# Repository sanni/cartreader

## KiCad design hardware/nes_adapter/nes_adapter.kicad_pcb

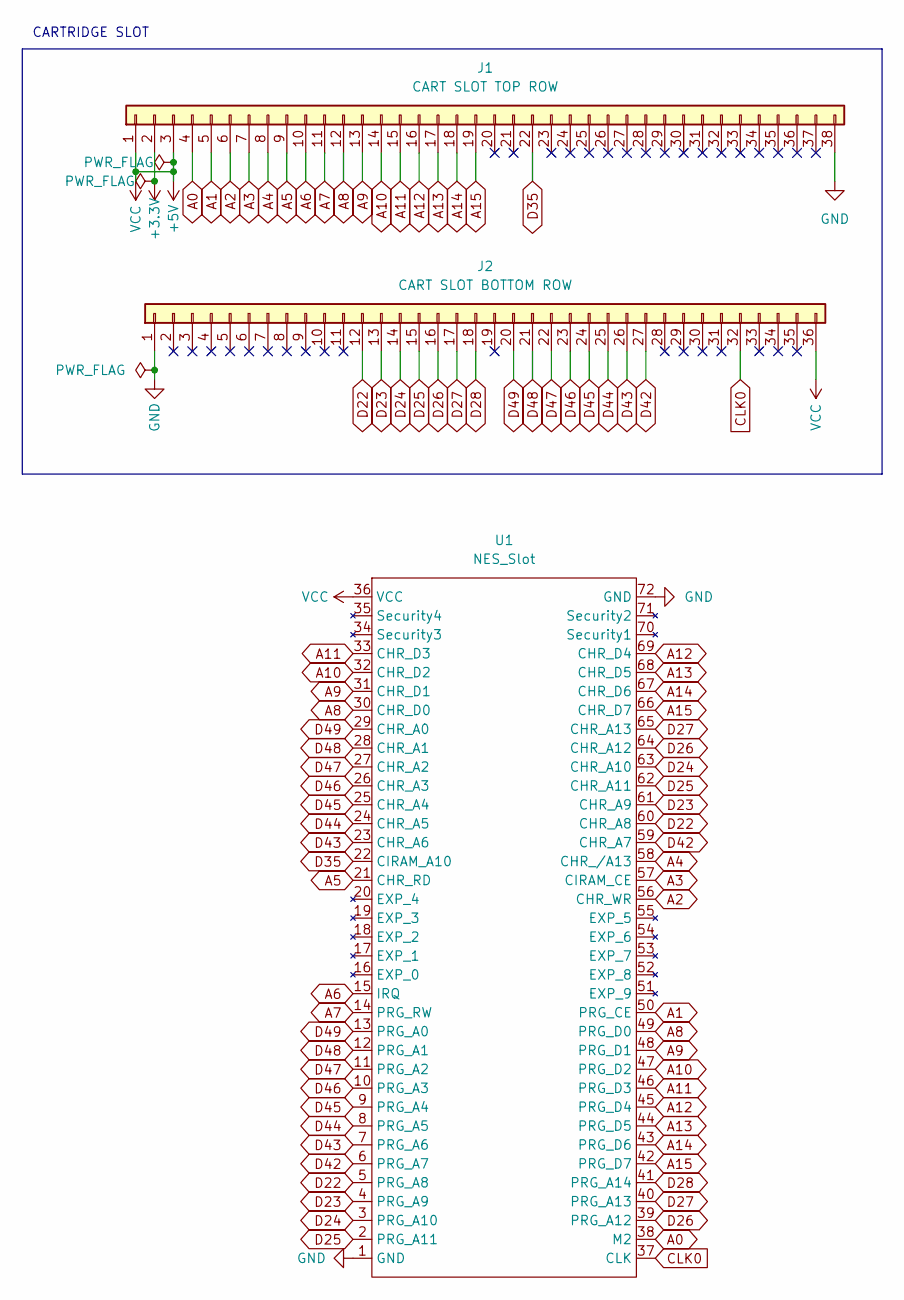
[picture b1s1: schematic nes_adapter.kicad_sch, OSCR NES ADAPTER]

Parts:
J1: CART SLOT TOP ROW; PinSocket_1x38_P2.54mm_Vertical
J2: CART SLOT BOTTOM ROW; PinSocket_1x36_P2.54mm_Vertical
U1: NES_Slot

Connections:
+3V3: J1.2
+5V: J1.1, J1.3, J2.36, U1.36 (VCC)
A0: J1.4, U1.38 (M2)
A1: J1.5, U1.50 (PRG_CE)
A2: J1.6, U1.56 (CHR_WR)
A3: J1.7, U1.57 (CIRAM_CE)
A4: J1.8, U1.58 (CHR_/A13)
A5: J1.9, U1.21 (CHR_RD)
A6: J1.10, U1.15 (IRQ)
A7: J1.11, U1.14 (PRG_RW)
A8: J1.12, U1.30 (CHR_D0), U1.49 (PRG_D0)
A9: J1.13, U1.31 (CHR_D1), U1.48 (PRG_D1)
A10: J1.14, U1.32 (CHR_D2), U1.47 (PRG_D2)
A11: J1.15, U1.33 (CHR_D3), U1.46 (PRG_D3)
A12: J1.16, U1.45 (PRG_D4), U1.69 (CHR_D4)
A13: J1.17, U1.44 (PRG_D5), U1.68 (CHR_D5)
A14: J1.18, U1.43 (PRG_D6), U1.67 (CHR_D6)
A15: J1.19, U1.42 (PRG_D7), U1.66 (CHR_D7)
CLK0: J2.32, U1.37 (CLK)
D22: J2.12, U1.5 (PRG_A8), U1.60 (CHR_A8)
D23: J2.13, U1.4 (PRG_A9), U1.61 (CHR_A9)
D24: J2.14, U1.3 (PRG_A10), U1.63 (CHR_A10)
D25: J2.15, U1.2 (PRG_A11), U1.62 (CHR_A11)
D26: J2.16, U1.39 (PRG_A12), U1.64 (CHR_A12)
D27: J2.17, U1.40 (PRG_A13), U1.65 (CHR_A13)
D28: J2.18, U1.41 (PRG_A14)
D35: J1.22, U1.22 (CIRAM_A10)
D42: J2.27, U1.6 (PRG_A7), U1.59 (CHR_A7)
D43: J2.26, U1.7 (PRG_A6), U1.23 (CHR_A6)
D44: J2.25, U1.8 (PRG_A5), U1.24 (CHR_A5)
D45: J2.24, U1.9 (PRG_A4), U1.25 (CHR_A4)
D46: J2.23, U1.10 (PRG_A3), U1.26 (CHR_A3)
D47: J2.22, U1.11 (PRG_A2), U1.27 (CHR_A2)
D48: J2.21, U1.12 (PRG_A1), U1.28 (CHR_A1)
D49: J2.20, U1.13 (PRG_A0), U1.29 (CHR_A0)
GND: J1.38, J2.1, U1.1 (GND), U1.72 (GND)

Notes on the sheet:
CARTRIDGE SLOT

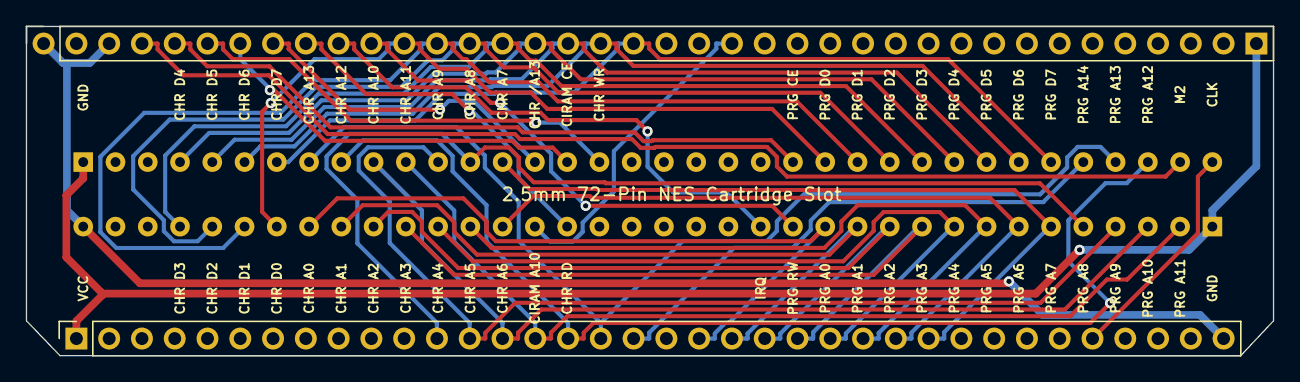
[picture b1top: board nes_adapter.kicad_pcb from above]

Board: 2 copper layers, 96.6 x 25.5 mm, 3 parts (0 on the bottom side), 35 nets.

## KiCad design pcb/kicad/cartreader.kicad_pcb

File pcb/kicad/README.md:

You can view the schematic and the PCB files using a free and open source programm called [KiCad](https://www.kicad.org/).

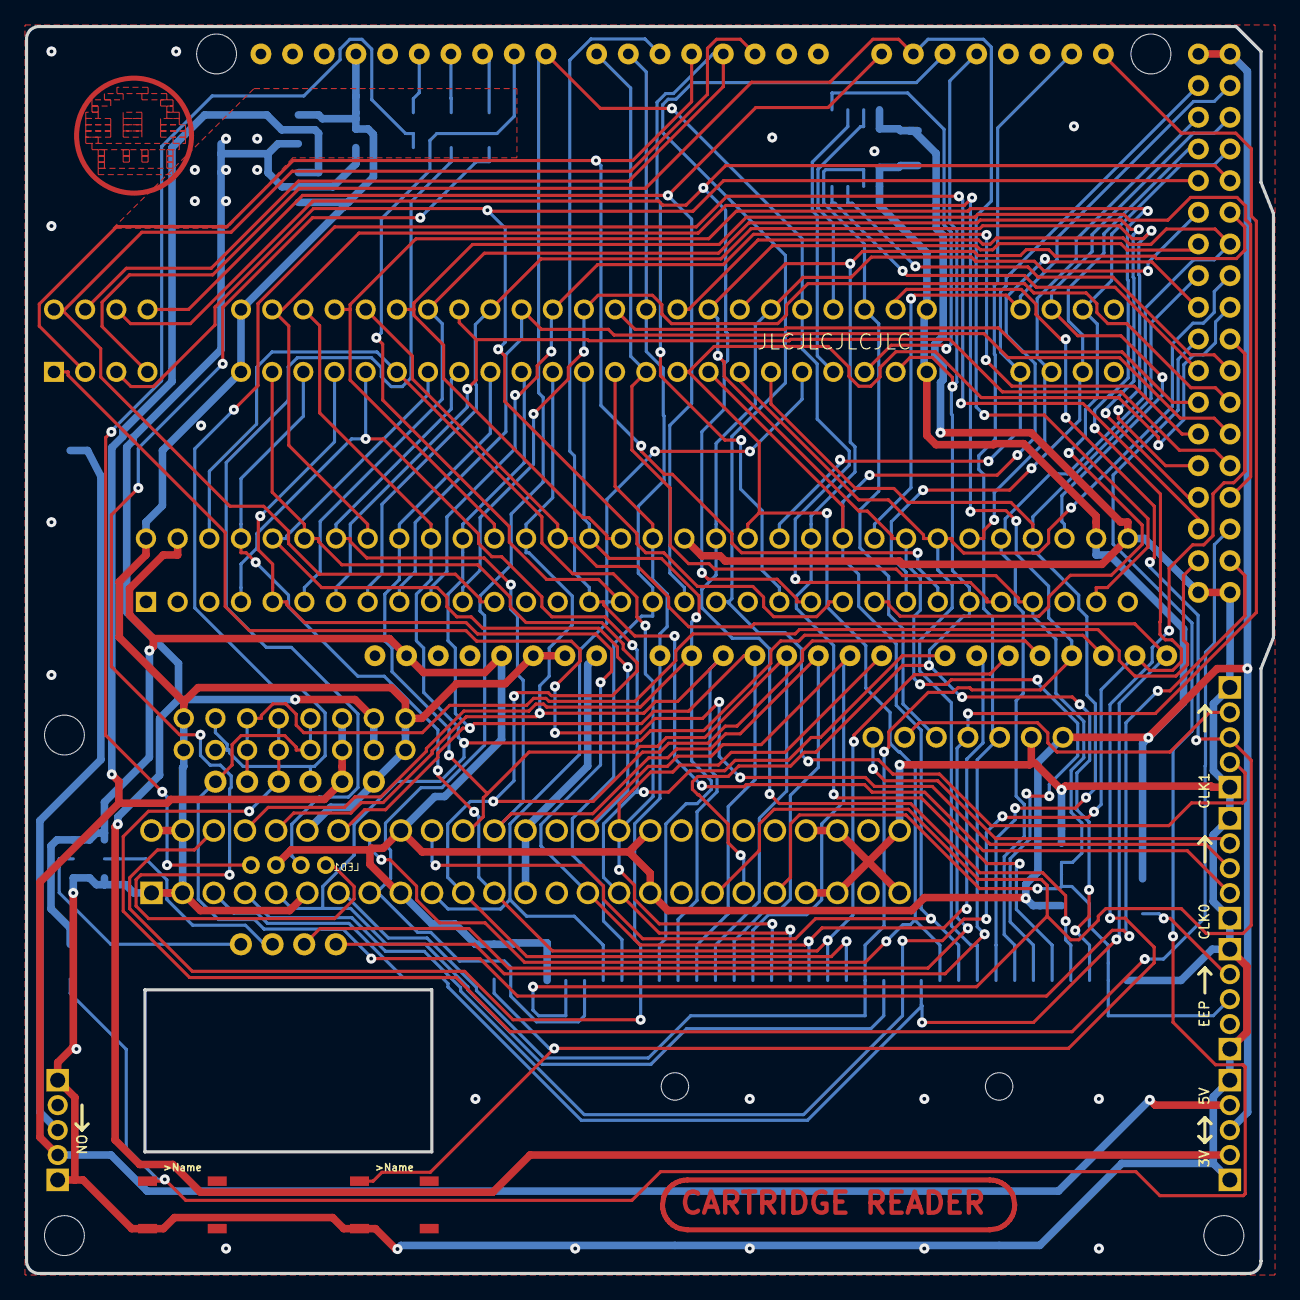
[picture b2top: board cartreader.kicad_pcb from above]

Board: 2 copper layers, 100.0 x 100.0 mm, 46 parts (0 on the bottom side), 85 nets.

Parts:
1K1, 10K1, 220R1, 1000R1: R-US_M1206; M1206
100NF1: C-USC1206; C1206
+22UF1: C-USC1206; C1206
@HOLE0, @HOLE1, @HOLE2, @HOLE3, @HOLE4: (no value)
ADCH1: 8x1F-H8.5; 1X08
ADCL1: 8x1F-H8.5; 1X08
AMS1117-3V3: SMD-AMS1117SOT223; SOT223
CIC1: PIC12F629_SIMPLE; PIC12F629
CLK0, CLK1: SWITCH-SPDT-2MMPTH; SWITCH-SPDT-2MM
CLOCKGEN1: CLOCKGEN_2.54; CLOCKGEN
CN2: THT-PINHEADER_1X6-CLEANBIG; 1X06-CLEANBIG
COMMUNICATION1: 8x1F-H8.5; 1X08
CONTROLLER1: SMD-SOLDER_PAD; SMD1,27-2,54
EEP1: SWITCH-SPDT-2MMPTH; SWITCH-SPDT-2MM
LED1: THT-PINHEADER_1X4_2MM-CLEANBIG; 1X04-CLEANSMALL
MEGADRIVE1: MD-CART_SLOT
OLED1: OLED_I2C-CLEANBIG; OLED_I2C
ONOFF1: SWITCH-SPDT-2MMPTH; SWITCH-SPDT-2MM
PAD1, PAD2, PAD3: SMD-SOLDER_PAD; SMD1,27-2,54
PINS1: 10x1F-H8.5; 1X10
POWER1: 8x1F-H8.5; 1X08
PWML1: 8x1F-H8.5; 1X08
R19, R20: R-US_M1206; M1206
S1, S2: MOMENTARY-SWITCH-SPST-SMD-5.2MM; TACTILE_SWITCH_SMD_5.2MM
SDCARD1: PINHD-2X8_2.54; 2X08
SJ2, SJ4: SJ2W; SJ_2
U$1: SNESCART_CONN_CLONE
U$2: N64-CART_SLOT_4
U$4: GBA-SLOT-BSMD; GBA-SLOT-B
USB5V1: SMD-SOLDER_PAD; SMD1,27-2,54
USBGND1: SMD-SOLDER_PAD; SMD1,27-2,54
VOLTAGE1: SWITCH-SPDT-2MMPTH; SWITCH-SPDT-2MM
XIO1: 18x2F-H8.5; 2X18

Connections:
/3V3: +22UF1.1, AMS1117-3V3.2, AMS1117-3V3.4, SDCARD1.3, SDCARD1.4, VOLTAGE1.1
/5V: AMS1117-3V3.3, CN2.5, ONOFF1.1, SDCARD1.5, SDCARD1.6, VOLTAGE1.3
/ADC0: ADCL1.1, MEGADRIVE1.49, U$1.17, U$2.P28, U$4.6
/ADC1: ADCL1.2, MEGADRIVE1.47, U$1.16, U$2.P29, U$4.7
/ADC2: ADCL1.3, MEGADRIVE1.45, U$1.15, U$2.P30, U$4.8
/ADC3: ADCL1.4, MEGADRIVE1.43, U$1.14, U$2.P32, U$4.9
/ADC4: ADCL1.5, MEGADRIVE1.41, U$1.13, U$2.P36, U$4.10
/ADC5: ADCL1.6, MEGADRIVE1.39, U$1.12, U$2.P37, U$4.11
/ADC6: ADCL1.7, MEGADRIVE1.37, U$1.11, U$2.P40, U$4.12
/ADC7: ADCL1.8, MEGADRIVE1.35, U$1.10, U$2.P41, U$4.13
/ADC8: ADCH1.1, MEGADRIVE1.4, U$1.9, U$2.P16, U$4.14
/ADC9: ADCH1.2, MEGADRIVE1.5, U$1.8, U$2.P15, U$4.15
/ADC10: ADCH1.3, MEGADRIVE1.36, U$1.7, U$2.P12, U$4.16
/ADC11: ADCH1.4, MEGADRIVE1.38, U$1.6, U$2.P11, U$4.17
/ADC12: ADCH1.5, MEGADRIVE1.40, U$1.85, U$2.P7, U$4.18
/ADC13: ADCH1.6, MEGADRIVE1.42, U$1.80, U$2.P5, U$4.19
/ADC14: ADCH1.7, MEGADRIVE1.44, U$1.79, U$2.P4, U$4.20
/ADC15: ADCH1.8, MEGADRIVE1.46, U$1.78, U$2.P3, U$4.21
/CICDATA0: CIC1.7, U$1.75
/CICDATA1: CIC1.6, U$1.24
/CICRSTSO: CIC1.5, U$1.25
/CLK: CLK0.2, U$1.1
/CLK0: CLK0.3, CLOCKGEN1.7
/CLK1: CLK1.3, CLOCKGEN1.6
/CLK2: CIC1.2, CLOCKGEN1.5, U$1.81
/CPUCLK: CLK1.2, U$1.82, U$2.P19, U$4.2
/PA0: MEGADRIVE1.53, U$1.28, XIO1.3
/PA1: MEGADRIVE1.56, U$1.90, XIO1.4
/PA2: MEGADRIVE1.59, U$1.29, XIO1.5
/PA3: MEGADRIVE1.62, U$1.91, XIO1.6
/PA4: MEGADRIVE1.25, U$1.30, XIO1.7
/PA5: MEGADRIVE1.24, U$1.92, XIO1.8
/PA6: MEGADRIVE1.23, U$1.3, XIO1.9
/PA7: MEGADRIVE1.22, U$1.87, XIO1.10
/PB0: CN2.1, SDCARD1.7, SDCARD1.8, XIO1.34
/PB1: CN2.2, SDCARD1.11, SDCARD1.12, XIO1.33
/PB2: CN2.3, SDCARD1.9, SDCARD1.10, XIO1.32
/PB3: CN2.4, SDCARD1.13, SDCARD1.14, XIO1.31
/PB4: LED1.4, R20.1
/PB5: LED1.3, R19.1
/PB6: 220R1.1, LED1.1
/PC0: MEGADRIVE1.52, U$1.19, U$2.P33, U$4.22, XIO1.18
/PC1: MEGADRIVE1.55, U$1.20, U$2.P35, U$4.23, XIO1.17
/PC2: MEGADRIVE1.58, U$1.21, U$4.24, XIO1.16
/PC3: MEGADRIVE1.61, U$1.22, U$4.25, XIO1.15
/PC4: MEGADRIVE1.60, U$1.70, U$4.26, XIO1.14
/PC5: MEGADRIVE1.57, U$1.71, U$4.27, XIO1.13
/PC6: MEGADRIVE1.54, U$1.72, U$4.28, XIO1.12
/PC7: MEGADRIVE1.51, U$1.73, U$4.29, XIO1.11
/PD7: 10K1.1, S1.1, XIO1.19
/PE3: CLK0.1, MEGADRIVE1.15, PWML1.6
/PE4: MEGADRIVE1.12, PWML1.3, U$1.89
/PE5: MEGADRIVE1.21, PWML1.4, U$1.88
/PG0: CIC1.3, XIO1.22
/PG1: CIC1.4, XIO1.21
/PG2: 1000R1.1, S2.1, XIO1.20
/PG5: MEGADRIVE1.26, PWML1.5, U$1.2
/PH0: COMMUNICATION1.5, MEGADRIVE1.27, U$1.26, U$2.P20, U$4.30
/PH1: CLK1.1, COMMUNICATION1.6, MEGADRIVE1.19
/PH3: MEGADRIVE1.17, PWML1.7, U$1.69, U$4.5
/PH4: CONTROLLER1.1, EEP1.2, MEGADRIVE1.29, PWML1.8, U$1.18, U$2.P21, U$4.31
/PH5: MEGADRIVE1.28, PINS1.10, U$1.74, U$2.P8, U$4.3
/PH6: MEGADRIVE1.16, PINS1.9, U$1.23, U$2.P10, U$4.4
/PJ0: COMMUNICATION1.7, MEGADRIVE1.31, U$1.4
/PJ1: COMMUNICATION1.8, MEGADRIVE1.18, U$1.86
/PL0: MEGADRIVE1.48, U$1.77, XIO1.30
/PL1: MEGADRIVE1.6, U$1.76, XIO1.29
/PL2: MEGADRIVE1.7, U$1.67, XIO1.28
/PL3: MEGADRIVE1.8, U$1.66, XIO1.27
/PL4: MEGADRIVE1.9, U$1.65, XIO1.26
/PL5: MEGADRIVE1.10, U$1.64, XIO1.25
/PL6: MEGADRIVE1.11, U$1.63, XIO1.24
/PL7: U$1.68, XIO1.23
/SCL: CLOCKGEN1.4, COMMUNICATION1.1, OLED1.3
/SDA: CLOCKGEN1.3, COMMUNICATION1.2, OLED1.4
/VCC: 1K1.1, 10K1.2, 100NF1.1, 1000R1.2, CIC1.1, CLOCKGEN1.1, LED1.2, MEGADRIVE1.34, MEGADRIVE1.63, PAD3.1, POWER1.2, POWER1.5, SJ2.3, SJ4.3, U$1.27, U$1.83, U$2.P9, U$2.P17, U$2.P34, U$2.P42, U$4.1, VOLTAGE1.2, XIO1.1, XIO1.2
/VIN: POWER1.8, U$2.P13, U$2.P38
GND: 100NF1.2, +22UF1.2, AMS1117-3V3.1, CIC1.8, CLK0.P$1, CLK1.P$1, CLOCKGEN1.2, CN2.6, EEP1.P$1, MEGADRIVE1.33, MEGADRIVE1.50, MEGADRIVE1.64, ONOFF1.P$1, PAD1.1, PAD2.1, PINS1.4, POWER1.6, POWER1.7, S1.3, S2.3, SDCARD1.1, SDCARD1.2, SDCARD1.15, SDCARD1.16, SJ2.1, SJ4.1, U$1.5, U$1.84, U$2.P1, U$2.P2, U$2.P6, U$2.P22, U$2.P23, U$2.P25, U$2.P26, U$2.P27, U$2.P31, U$2.P47, U$2.P48, U$2.P50, U$4.32, U$4.SHIELD_3, U$4.SHIELD_4, USBGND1.1, VOLTAGE1.P$1, XIO1.35, XIO1.36
unnamed: 1K1.2, EEP1.1
unnamed: 220R1.2, PINS1.6
unnamed: OLED1.1, SJ2.2
unnamed: OLED1.2, SJ4.2
unnamed: ONOFF1.2, USB5V1.1
unnamed: PINS1.7, R19.2
unnamed: PINS1.8, R20.2
